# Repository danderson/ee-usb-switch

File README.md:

# ee-usb-switch
USB-controlled load switches

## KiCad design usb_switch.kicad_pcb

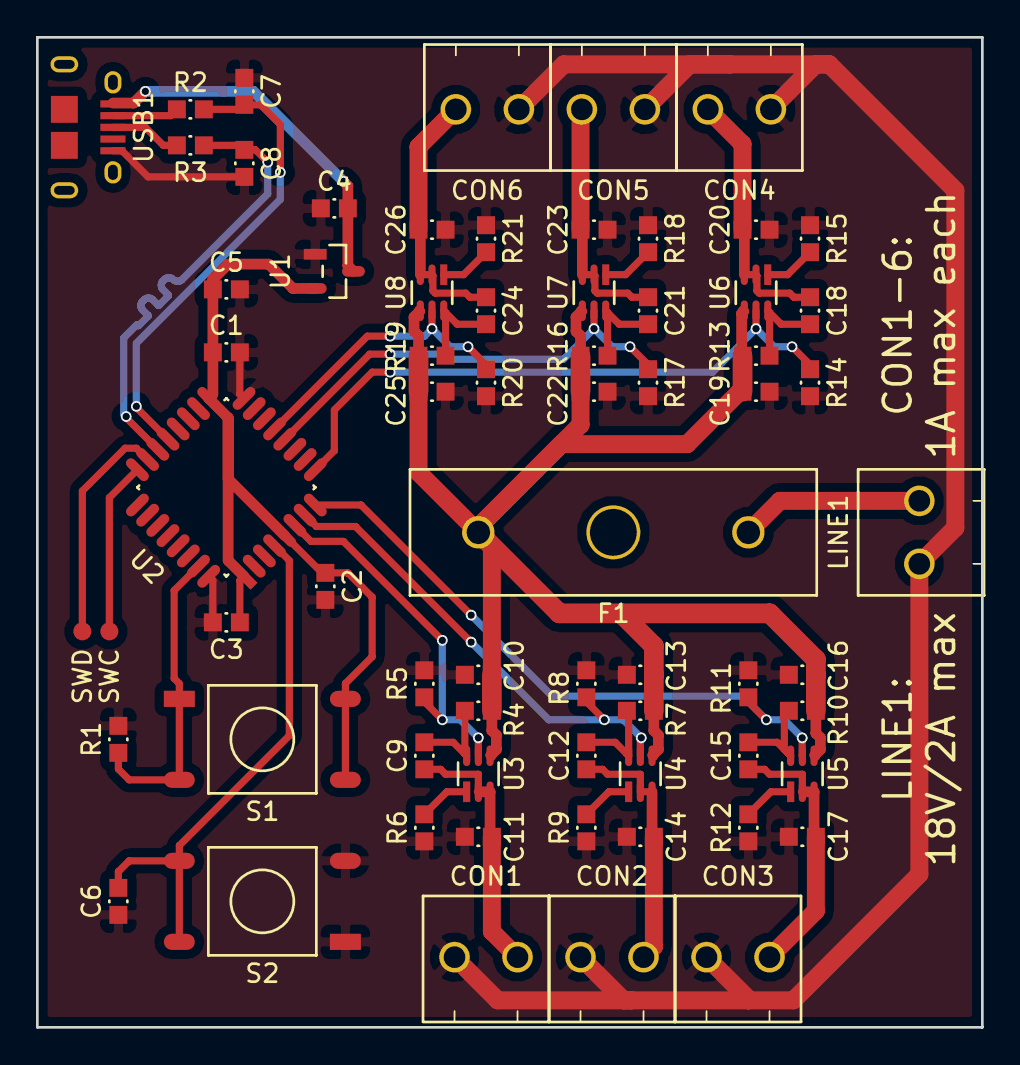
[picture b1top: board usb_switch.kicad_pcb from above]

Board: 2 copper layers, 52.5 x 55.0 mm, 68 parts (0 on the bottom side), 37 nets.

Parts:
C1, C2, C3, C6: 100nF; Capacitor_0603
C4, C9, C11, C12, C14, C15, C17, C18, C20, C21, C23, C24, C26: 1µF; Capacitor_0603
C5, C10, C13, C16, C19, C22, C25: 10µF; Capacitor_0603
C7, C8: 47pF; Capacitor_0603
CON1, CON2, CON3, CON4, CON5, CON6: 2_Post_Terminal; 2_Post_Terminal_OSTTE020104
F1: 2A; Fuse_Block
LINE1: 2_Post_Terminal; 2_Post_Terminal_OSTTE020104
R1, R4, R5, R7, R8, R10, R11, R13, R14, R16, R17, R19, R20: 10k; Resistor_0603
R2, R3: 22R; Resistor_0603
R6, R9, R12, R15, R18, R21: 2k; Resistor_0603
S1, S2: Switch_SPST; Switch_SPST_TL3301NF160QG
TP1: SWD; Test_Point_Test_Point_1mm
TP2: SWC; Test_Point_Test_Point_1mm
U1: AP2120N; AP2120N_SOT23-3
U2: STM32F042K6T6; STM32F042K6T6_32-QFP
U3, U4, U5, U6, U7, U8: Si1869DH; Si1869DH_SC70-6
USB1: USB; USB_Micro_SMD_RA

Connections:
+3.3V: C1.2, C2.2, C3.2, C5.2, S1.3, S1.4, U1.2, U2.1, U2.5, U2.17
+5V: C4.2, U1.3, USB1.1
/D+: R2.1, USB1.2
/D-: R3.1, USB1.3
/Switch 1/SW: R5.2, U2.6, U3.5
/Switch 2/SW: R8.2, U2.7, U4.5
/Switch 3/SW: R11.2, U2.8, U5.5
/Switch 4/SW: R14.2, U2.9, U6.5
/Switch 5/SW: R17.2, U2.12, U7.5
/Switch 6/SW: R20.2, U2.13, U8.5
/USB_D+: C7.2, R2.2, U2.21
/USB_D-: C8.2, R3.2, U2.22
GND: C1.1, C2.1, C3.1, C4.1, C5.1, C6.2, C7.1, C8.1, C10.1, C11.2, C13.1, C14.2, C16.1, C17.2, C19.1, C20.2, C22.1, C23.2, C25.1, C26.2, CON1.2, CON2.2, CON3.2, CON4.2, CON5.2, CON6.2, LINE1.2, R1.1, R5.1, R6.1, R8.1, R9.1, R11.1, R12.1, R14.1, R15.1, R17.1, R18.1, R20.1, R21.1, S2.1, S2.2, U1.1, U2.16, U2.32, USB1.5
Line: C10.2, C13.2, C16.2, C19.2, C22.2, C25.2, F1.2, R4.1, R7.1, R10.1, R13.1, R16.1, R19.1, U3.4, U4.4, U5.4, U6.4, U7.4, U8.4
unnamed: C6.1, S2.3, S2.4, U2.4
unnamed: C9.2, R4.2, U3.6
unnamed: C9.1, C11.1, CON1.1, U3.2, U3.3
unnamed: C12.1, C14.1, CON2.1, U4.2, U4.3
unnamed: C12.2, R7.2, U4.6
unnamed: C15.1, C17.1, CON3.1, U5.2, U5.3
unnamed: C15.2, R10.2, U5.6
unnamed: C18.1, C20.1, CON4.1, U6.2, U6.3
unnamed: C18.2, R13.2, U6.6
unnamed: C21.1, C23.1, CON5.1, U7.2, U7.3
unnamed: C21.2, R16.2, U7.6
unnamed: C24.1, C26.1, CON6.1, U8.2, U8.3
unnamed: C24.2, R19.2, U8.6
unnamed: F1.1, LINE1.1
unnamed: R1.2, S1.1, S1.2, U2.31
unnamed: R6.2, U3.1
unnamed: R9.2, U4.1
unnamed: R12.2, U5.1
unnamed: R15.2, U6.1
unnamed: R18.2, U7.1
unnamed: R21.2, U8.1
unnamed: TP1.1, U2.23
unnamed: TP2.1, U2.24

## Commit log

2015-11-17 Add the kidraw parts library.
    The library is incomplete, because kidraw is incomplete. But it's a
    start.
2015-11-17 New Kidraw file organization.
    Kidraw now hides all the library files in the footprints
    subdirectory.
2015-11-17 Small tweaks to the part library.
2015-11-17 Add schematic.
    The schematic is failing ERC for reasons I don't understand yet.
2015-11-18 Fix ERC for the schematic.
2015-11-18 Correct some wiring faults.
    - Switch Slew and Bias pins on the switch IC.
    - Rename the "+12V" rail to "Line".
    - Remove unnecessary power flags to appease ERC.
2015-11-18 Add a .gitignore to forget about backup and cache files.
2015-11-18 Readd missing junction on switch schematic.
2015-11-18 Define some basic footprints.
2015-11-19 Update parts
2015-11-29 Reimplement the part generator with the new Kicad.
    The project should now have all the schematics and footprints
    it'll need for completion, although the USB footprint still needs
    work.
2015-12-02 A bunch of work on schematic and layout.
2015-12-04 More hacking on the PCB layout, also adding a fuse component.
2015-12-04 Finish routing the PCB.
2015-12-05 Sent to fab.

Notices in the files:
usb_switch.kicad_pcb:
(c) 2015 David Anderson
License: Creative Commons Attribution 4.0 International
